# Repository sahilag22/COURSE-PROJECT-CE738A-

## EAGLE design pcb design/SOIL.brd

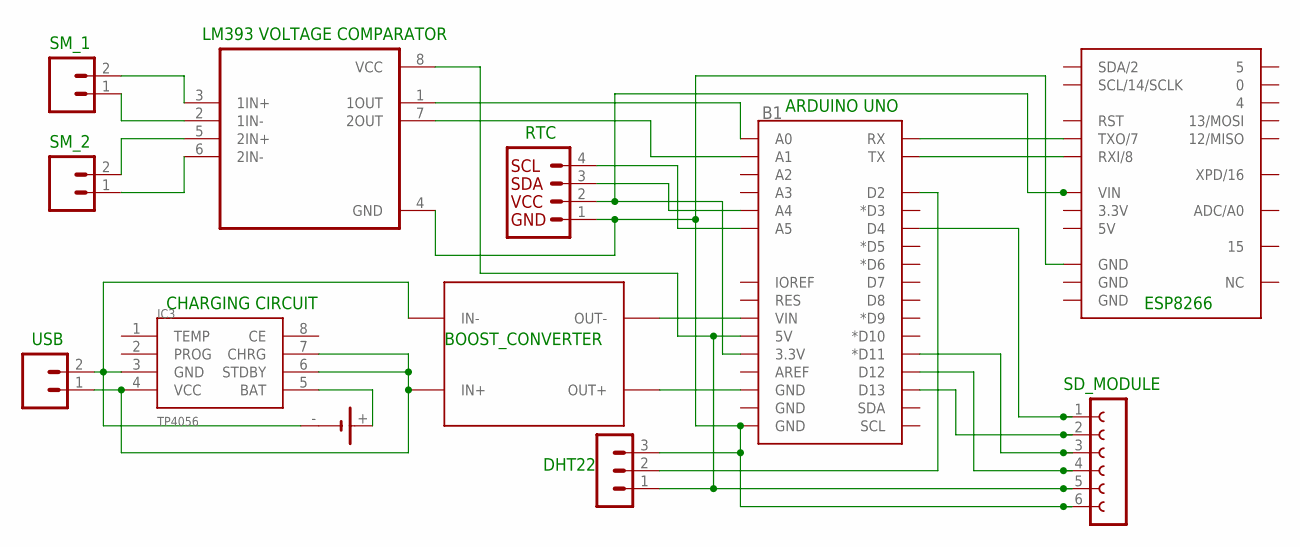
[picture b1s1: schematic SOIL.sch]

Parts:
B1: ARDUINO_UNO_R3_SHIELDUNO_R3_SHIELD_NOLABELS_LOCK; UNO_R3_SHIELD_NOLABELS_LOCK
B2: SPARKFUN_ESP8266_THING_DEV
G1: SL-150-1/2AA/PT
IC3: TP4056; SOP-8
J3, J5, J6: CONN_02; 1X02
J4: I2C_STANDARDUNITEST; 1X04_UNITEST
SV3: MA03-1
SV4: FE06-1; FE06
U1: LM393D; SOIC127P600X175-8N
U$1: DC-DC-STEP-UP-MT3608

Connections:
3.3V: B2.3.3V
5V: B2.5V
GND: B2.GND@2 (GND), B2.GND@3 (GND)
unnamed: B1.VIN, U$1.OUT-
unnamed: B1.GND@2 (GND), U$1.OUT+
unnamed: G1.-, IC3.3 (GND), J5.2, U$1.IN-
unnamed: IC3.4 (VCC), IC3.6 (STDBY), IC3.7 (CHRG), J5.1, U$1.IN+
unnamed: G1.+, IC3.5 (BAT)
unnamed: J6.2, U1.3 (1IN+)
unnamed: B1.D4, SV4.1
unnamed: B1.D13, SV4.2
unnamed: B1.D11 (*D11), SV4.3
unnamed: B1.D12, SV4.4
unnamed: B1.5V, SV3.1, SV4.5, U1.8 (VCC)
unnamed: B1.GND@0 (GND), B2.GND@1 (GND), J4.1, SV3.3, SV4.6, U1.4 (GND)
unnamed: B1.A5, J4.4
unnamed: B1.A4, J4.3
unnamed: B1.3.3V, B2.VIN, J4.2
unnamed: B1.RX, B2.TX (TXO/7)
unnamed: B1.TX, B2.RX (RXI/8)
unnamed: B1.D2, SV3.2
unnamed: J6.1, U1.2 (1IN-)
unnamed: B1.A1, U1.7 (2OUT)
unnamed: B1.A0, U1.1 (1OUT)
unnamed: J3.2, U1.5 (2IN+)
unnamed: J3.1, U1.6 (2IN-)

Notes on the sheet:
SM_1
SM_2
BOOST_CONVERTER
USB
LM393 VOLTAGE COMPARATOR
RTC
CHARGING CIRCUIT
ARDUINO UNO
DHT22
SD_MODULE
ESP8266

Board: 2 copper layers, 12 parts (0 on the bottom side), 24 nets, no tracks yet.

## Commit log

2023-08-25 INITIAL COMMITS

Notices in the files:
parts and their libraries:
SparkFun-Boards: Licensing: Creative Commons ShareAlike 4.0 International - https://creativecommons.org/licenses/by-sa/4.0
